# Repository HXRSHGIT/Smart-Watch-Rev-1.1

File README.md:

# Smart Watch Rev 1.1 — HealthOS Band R&D

R&D repository for the client's **HealthOS Band** (WHOOP-style wellness band with a hidden 64×32 OLED).
Source brief: [`docs/HARDWARE_ENGINEER_HANDOFF_REQUIREMENTS.md`](docs/HARDWARE_ENGINEER_HANDOFF_REQUIREMENTS.md) (copied unchanged).

Done by Harsh Thakur.

## Current design - Iteration 1

The Iteration 1 board is a **battery-less, bench-powered engineering PCB** (5 V on two pogo pads or a 2.54 mm header, no cell fitted) built around **nRF54L15 + nPM1300 + MAX86141 (SFH 7016 emitters, 2 x VEMD8080 photodiodes) + BMI270 + MAX30208 + MX25R3235F flash + a Johanson chip antenna**. Firmware is flashed and debugged over SWD (Tag-Connect). The 10-page KiCad 9 schematic, its checks and the board file are in **[`hardware/schematic/`](hardware/schematic/README.md)**; the board is designed to JLCPCB's stated limits (4 layers, 0.8 mm, ENIG), see **[`hardware/JLCPCB_DESIGN_RULES.md`](hardware/JLCPCB_DESIGN_RULES.md)**. Layout (placement and routing) has not been done yet, and the design is not a fabrication-ready or sourcing-verified BOM.

This replaces the earlier 2026-10-18 baseline (ESP32-C3-MINI-1 + MAX30102 + MAX30208, USB-powered). That baseline is kept only as history in [Iteration 1 decision](docs/ITERATION_1_DECISION.md), [Iteration 1 schematic connection plan](docs/ITERATION_1_SCHEMATIC_FLOW.md) and [Component Selection](docs/COMPONENT_SELECTION.md); those three documents describe parts that are no longer on the board.

The documents under `research/` describe the earlier full-wearable investigations. Their parts and performance estimates are **not the current Iteration 1 BOM**. The original client brief remains intact as the longer-term product reference.

## How this repo is organised

`main` holds the brief, this index, the R&D map **and all research merged in** (folders below). Each topic also stays on its **own `rnd/*` branch** for a separate view.

| Branch | Folder | Covers (brief §) |
|---|---|---|
| `rnd/components` | [`research/components/`](research/components/) | §8 — every candidate part plus alternatives, full detail (`COMPONENTS.md`) |
| `rnd/mcu-ble` | [`research/mcu-ble/`](research/mcu-ble/) | §4.6, §8 — nRF5340 vs nRF54, BLE security, DFU, antenna |
| `rnd/storage-nfc-dft` | [`research/storage-nfc-dft/`](research/storage-nfc-dft/) | §4.6, §8 — external flash, active NFC, SWD, production test |
| `rnd/power-battery` | [`research/power-battery/`](research/power-battery/) | §4.7, §8 — power tree, battery sizing, battery-life model, pogo charging, peaks |
| `rnd/display-haptics` | [`research/display-haptics/`](research/display-haptics/) | §4.4, §4.5 — OLED module, dead-front, back-power, LRA and driver |
| `rnd/optical-ppg` | [`research/optical-ppg/`](research/optical-ppg/) | §4.1, §8 — PPG HR, SpO2, optical stack, crosstalk |
| `rnd/sensors` | [`research/sensors/`](research/sensors/) | §4.1 — IMU, pressure and vent, skin temperature, time sync |
| `rnd/algorithms` | [`research/algorithms/`](research/algorithms/) | §4.2, §4.3, §5 — activity, calories, sleep, HRV and other P1 algorithms |
| `rnd/validation` | [`research/validation/`](research/validation/) | §13–15 — test plan, compliance, mechanical, RF, water and sweat |

## Earlier wearable R&D findings (historical, not the Iteration 1 baseline)

These findings are retained as research history, including assumptions and claims requiring further verification. In particular, the original PPG pulse limits, PVLED headroom reasoning, BMI270 current, NFC power assumptions and battery estimates must be rechecked before reuse. See the current decision above for what will actually be fitted now.

1. **Battery life is a PPG-settings decision.** Same hardware: ≈ 5 / 10 / 29 mAh per day for lean / typical / continuous-100-sps profiles → 5 days needs ≈ 32 / 61 / 184 mAh. Suggested target: 5 days on ≈ 150 mAh with adaptive PPG (`rnd/power-battery`).
2. **SoC: nRF54L15** (CSP if HDI is available) instead of nRF5340 — saves ≈ 50 mm²; battery difference ≈ 2 µA (`rnd/mcu-ble`).
3. **One 1.8 V digital rail.** MAX86141 is 1.8 V SPI, so swap the 3 V-only W25Q32RV flash for Macronix MX25R3235F (`rnd/storage-nfc-dft`).
4. **PPG LED supply needs ≥ 3.1 V** and cannot come from the nPM1300 bucks — VBAT direct (HR pauses near empty) or a small boost (`rnd/power-battery`, `rnd/optical-ppg`).
5. **Drop the active NFC reader** (no use case, ≈ 400 mA peak); the SoC's passive NFC tag gives tap-to-pair for free (`rnd/storage-nfc-dft`).
6. **BMI270 always-on accel (≈ 210 µA, verify) is a top load**, and it cannot do wrist-raise and tap at the same time — consider a low-power wake accelerometer (`rnd/sensors`, `rnd/display-haptics`).
7. **Stealth dead-front is not readable in direct sun**; an AR coating is the biggest improvement (`rnd/display-haptics`).
8. **SpO2 skin-tone bias is documented** — validate per Monk skin-tone group + ITA following FDA's 2025 draft study design (`rnd/optical-ppg`).
9. **Calories are the weakest output industry-wide** (27–93 % median error in published tests) — label as estimates (`rnd/algorithms`).
10. **§13 gates → 25 concrete tests**; wellness position depends on claims; water target at least IPX7 (`rnd/validation`).

## Longer-term wearable R&D map

Legend: **R&D** = open question, needs study or experiment · **Design** = known engineering, needs careful execution · **Owner** = client decision, not engineering.

| § | Point | Class | Why |
|---|---|---|---|
| 2 | Stealth dead-front vs visible OLED, same PCB | **R&D** | Transmission vs off-state blackness trade; needs material samples and measurement |
| 3 | Present all health outputs as estimates | Owner | Wording and claims policy; the sentence is cut off in the brief |
| 4.1 | Continuous / resting HR | **R&D** | Wrist PPG motion artifact; LED current vs battery |
| 4.1 | Workout HR and zones | **R&D** | HR accuracy during motion is the hardest PPG problem |
| 4.1 | Spot + sleep SpO2 | **R&D** | Reflective wrist SpO2 needs red/IR calibration against a reference; skin-tone bias |
| 4.1 | Skin temperature trend | **R&D** | Thermal isolation from PCB and battery heat; trend vs absolute |
| 4.1 | Motion data | Design | BMI270 is mature; orientation and FIFO setup |
| 4.1 | Pressure for floors | **R&D** | Waterproof breathable vent; sensitivity to wrist movement and temperature |
| 4.1 | Raw data access | Design | Logging and streaming bandwidth over BLE and flash |
| 4.1 | Sensor time sync | **R&D** | Common timebase across AFE, IMU and MCU FIFOs |
| 4.2 | Steps / distance / active min | Design | Known algorithms; tuning for wrist placement |
| 4.2 | Calories | **R&D** | Model choice (HR + motion + profile); estimate only |
| 4.2 | Floors / elevation | **R&D** | Barometer + IMU fusion |
| 4.2 | Activity classification + confidence | **R&D** | Needs a labelled dataset and an on-device model budget |
| 4.3 | Sleep detection / duration | **R&D** | Actigraphy + HR; validation vs reference |
| 4.3 | HW readiness for HRV / RR / stages | **R&D** | Sets PPG sample rate and timing jitter requirements now |
| 4.4 | 64×32 OLED module choice | **R&D** | Exact orderable module, flex, cover stack, outdoor readability |
| 4.4 | No back-power when display off | Design | Load switch + I/O state; measure leakage |
| 4.4 | Wake by gesture / tap | **R&D** | False-wake rate vs IMU power |
| 4.5 | LRA selection + patterns | **R&D** | Size, resonance, peak current, mounting in a thin band |
| 4.6 | BLE Android/iOS | Owner | Platforms to support |
| 4.6 | Secure pairing + authenticated DFU | Design | MCUboot / nRF Connect SDK; key management |
| 4.6 | External flash logging | Design | Capacity sizing vs offline days |
| 4.6 | SWD + production test access | Design | Pad plan, fixture |
| 4.7 | Battery capacity vs 5–7 days | **R&D** | Needs a duty-cycle power model, then a cell that fits the enclosure |
| 4.7 | Reversible pogo, faults | **R&D** | Bridge vs ideal-diode orientation fix, contact heating, ESD |
| 4.7 | Concurrent peak load | **R&D** | PPG pulses + radio + flash + haptic + NFC on a small cell |
| 4.7 | Charging limits | Design | Follow the cell datasheet; NTC wiring to nPM1300 |
| 5 | P1: HRV, RR, recovery, GPS, falls | **R&D** | Algorithm work; HW must not block it |
| 8 | MCU choice (nRF5340 vs nRF54) | **R&D** | Trade study before schematic freeze |
| 8 | Active NFC (ST25R210) | **R&D** | Use case unknown; power and antenna cost |
| 8 | Separate optical / NFC / display rails | **R&D** | Depends on the power model |
| 13 | Acceptance gates | Design | Test plan and fixtures per gate |

## Gaps in the brief

- Sections **6, 7, 9, 10, 11 and 12 are missing** (numbering jumps 5 → 8 → 13). Probably owner decisions, targets and deliverables. Ask the client.
- §3 is cut off mid-sentence: "…must be presented as estimates until the complete product".
- Open owner decisions: phone platforms, battery-life target, NFC use case, display module, water-resistance target.

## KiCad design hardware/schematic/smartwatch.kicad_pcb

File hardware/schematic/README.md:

# HealthOS Band main board: KiCad schematic

Done by Harsh Thakur.

KiCad 9 project, hierarchical. Open `smartwatch.kicad_pro`.

The sheets are drawn the way a person draws them: real wires between parts, left-to-right signal flow, frames with headings, blue designer notes, one ground symbol per group. Net labels are used only where a wire cannot reach: the I2C pair at the second chip on the sensors sheet, and on the root page the second receiver of the SPI bus (memory) and of the I2C bus (power), 10 labels. Bus test points sit on the sheets that own the bus. The rules are in `STYLE_GUIDE.md`; the datasheet review is in `REVIEW.md`. Each sheet is a script in `tools/sheets/`. Supply rails are power symbols, so they connect by name across sheets.

## Sheets

| Sheet | File | Contents | State |
|---|---|---|---|
| Root | `smartwatch.kicad_sch` | sheet blocks and the signals between them | done |
| Charging input | `input_protection.kicad_sch` | two pogo pads, OCVPB21-13F6, RLIM, COUT, FLAG pull-up | done |
| LED supply | `led_supply.kicad_sch` | TPS61240 5 V boost, 0 Ohm links to VLED (boost or VSYS) | done |
| MCU | `mcu.kicad_sch` | nRF54L15 (3 units), decoupling, DC/DC, crystals, reset, debug | done |
| RF | `rf.kicad_sch` | Nordic match network, antenna tee, Johanson antenna | done |
| Optical | `optical.kicad_sch` | MAX86141, SFH 7016, 2 x VEMD8080 | done |
| Sensors | `sensors.kicad_sch` | BMI270, MAX30208, I2C pull-ups | done |
| Test | `test.kicad_sch` | Tag-Connect SWD pads, test points | done |
| Power | `power.kicad_sch` | nPM1300 (QFN32), L6, caps, battery connector, NTC, ship-mode button | done |
| Memory | `memory.kicad_sch` | MX25R3235F (8-land USON), CS# pull-up, SPI test points | done |

## Rebuild and check

```
python tools/gen_footprints.py     # custom footprints -> libs/smartwatch.pretty
python tools/build.py              # symbols and sheets
python tools/check.py              # ERC + netlist vs expected + pin table + footprint pads
python tools/lint.py               # wire crossings and net labels per sheet
python tools/pinmap.py             # PIN_MAP.md and BOM.csv
python tools/dev.py mcu A3 110     # preview one sheet as build/dev/mcu.png
```

`check.py` needs `kicad-cli` (KiCad 9). It prints `ALL CHECKS PASSED` or the list of differences.

## What the check covers

1. KiCad ERC on the whole hierarchy: zero messages.
2. Every pin of the nRF54L15, nPM1300, MX25R3235F, MAX86141, SFH 7016, VEMD8080, BMI270, MAX30208, TPS61240, OCVPB21, antenna, battery connector, button and programming pads is on the net the requirements document says. The expected table is typed separately from the build script.
3. Every two-pin part by reference (both nets; the pin order of a passive does not matter, so the check follows each chain of parts from the nets it already knows), 61 of them. Internal nets are compared by connectivity, not by name, because wired nets carry no label.
4. The nRF54L15 symbol has the same 49 pin numbers and names as the datasheet pin table (`data/nrf54l15_qfn48_pins.csv`).
5. Every footprint pad matches the symbol pins (stock and custom footprints).
6. No net has a single pin.

## nRF54L15 pin plan

| Pins | Use |
|---|---|
| P2.01 SCK, P2.02 MOSI, P2.04 MISO | SPI bus (SPIM00, dedicated pins) to MAX86141 and the flash |
| P2.05 | chip select, MAX86141 |
| P2.00 | chip select, flash |
| P0.04 SCL, P0.03 SDA | I2C (TWIM30) to BMI270, MAX30208 and the nPM1300 (0x6B) |
| P0.01, P0.02 | BMI270 INT1, BMI270 INT2 (P0.00 is free: the MAX86141 INT is not wired, see `../JLCPCB_DESIGN_RULES.md`) |
| P2.03 | MAX30208 alarm (GPIO0) |
| P1.08 | nPM1300 interrupt (GPIO1) |
| P2.06 | OCVPB21 FLAG |
| P2.08 | LED boost enable |
| P2.09, P2.10 | free (the MAX86141 GPIO1 and GPIO2 are not wired) |
| P2.07 | SWO (trace output to the test pads) |
| P1.00, P1.01 | 32.768 kHz crystal |
| P1.02, P1.03 | NFC pins, unused |
| P1.04 to P1.07, P1.09 to P1.14 | unused (errata 100 on power-on shorts) |

## Known open items (also in `../REQUIREMENTS_FROM_DATASHEETS.md` section 12)

- nPM1300 and flash datasheets are not saved yet, so those two sheets and the power budget are not built.
- Footprint status is in `../FOOTPRINT_AUDIT.md`. Still open: the OCVPB21 dot-to-A1 link (confirm on the first parts), the VEMD8080 anode pad (closed by decision, prove with a diode test on a sample part), the pogo pad size (dock vendor), J4 (not fitted).
- Tag-Connect TC2030 pin order (1 VTREF, 2 SWDIO, 3 nRESET, 4 SWDCLK, 5 GND, 6 SWO) is confirmed against the TC2030-CTX cable drawing.
- Passive part numbers are not chosen yet; values and ratings come from the datasheets.

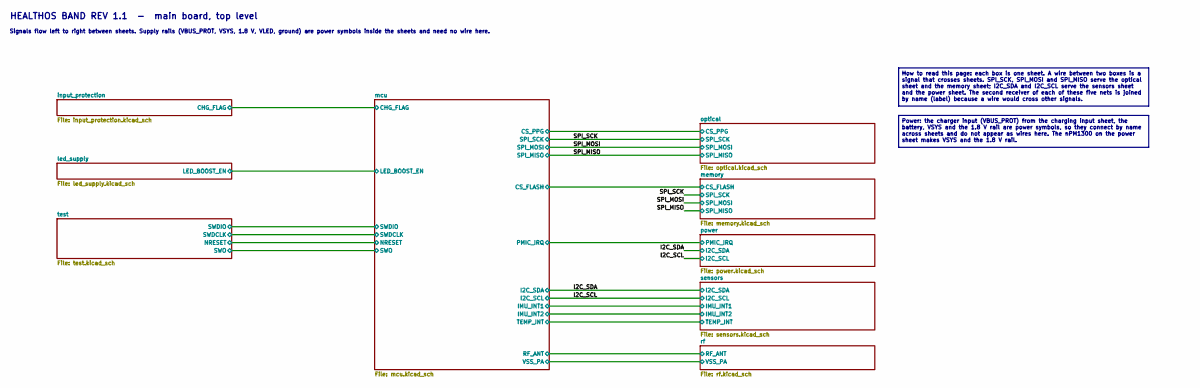
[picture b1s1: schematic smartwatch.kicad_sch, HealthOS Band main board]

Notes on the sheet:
HEALTHOS BAND REV 1.1 - main board, top level
Signals flow left to right between sheets. Supply rails (VBUS_PROT, VSYS, 1.8 V, VLED, ground) are power symbols inside the sheets and need no wire here.
How to read this page: each box is one sheet. A wire between two boxes is a signal that crosses sheets. SPI_SCK, SPI_MOSI and SPI_MISO serve the optical sheet and the memory sheet; I2C_SDA and I2C_SCL serve the sensors sheet and the power sheet. The second receiver of each of these five nets is joi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
Power: the charger input (VBUS_PROT) from the charging input sheet, the battery, VSYS and the 1.8 V rail are power symbols, so they connect by name across sheets and do not appear as wires here. The nPM1300 on the power sheet makes VSYS and the 1.8 V rail.

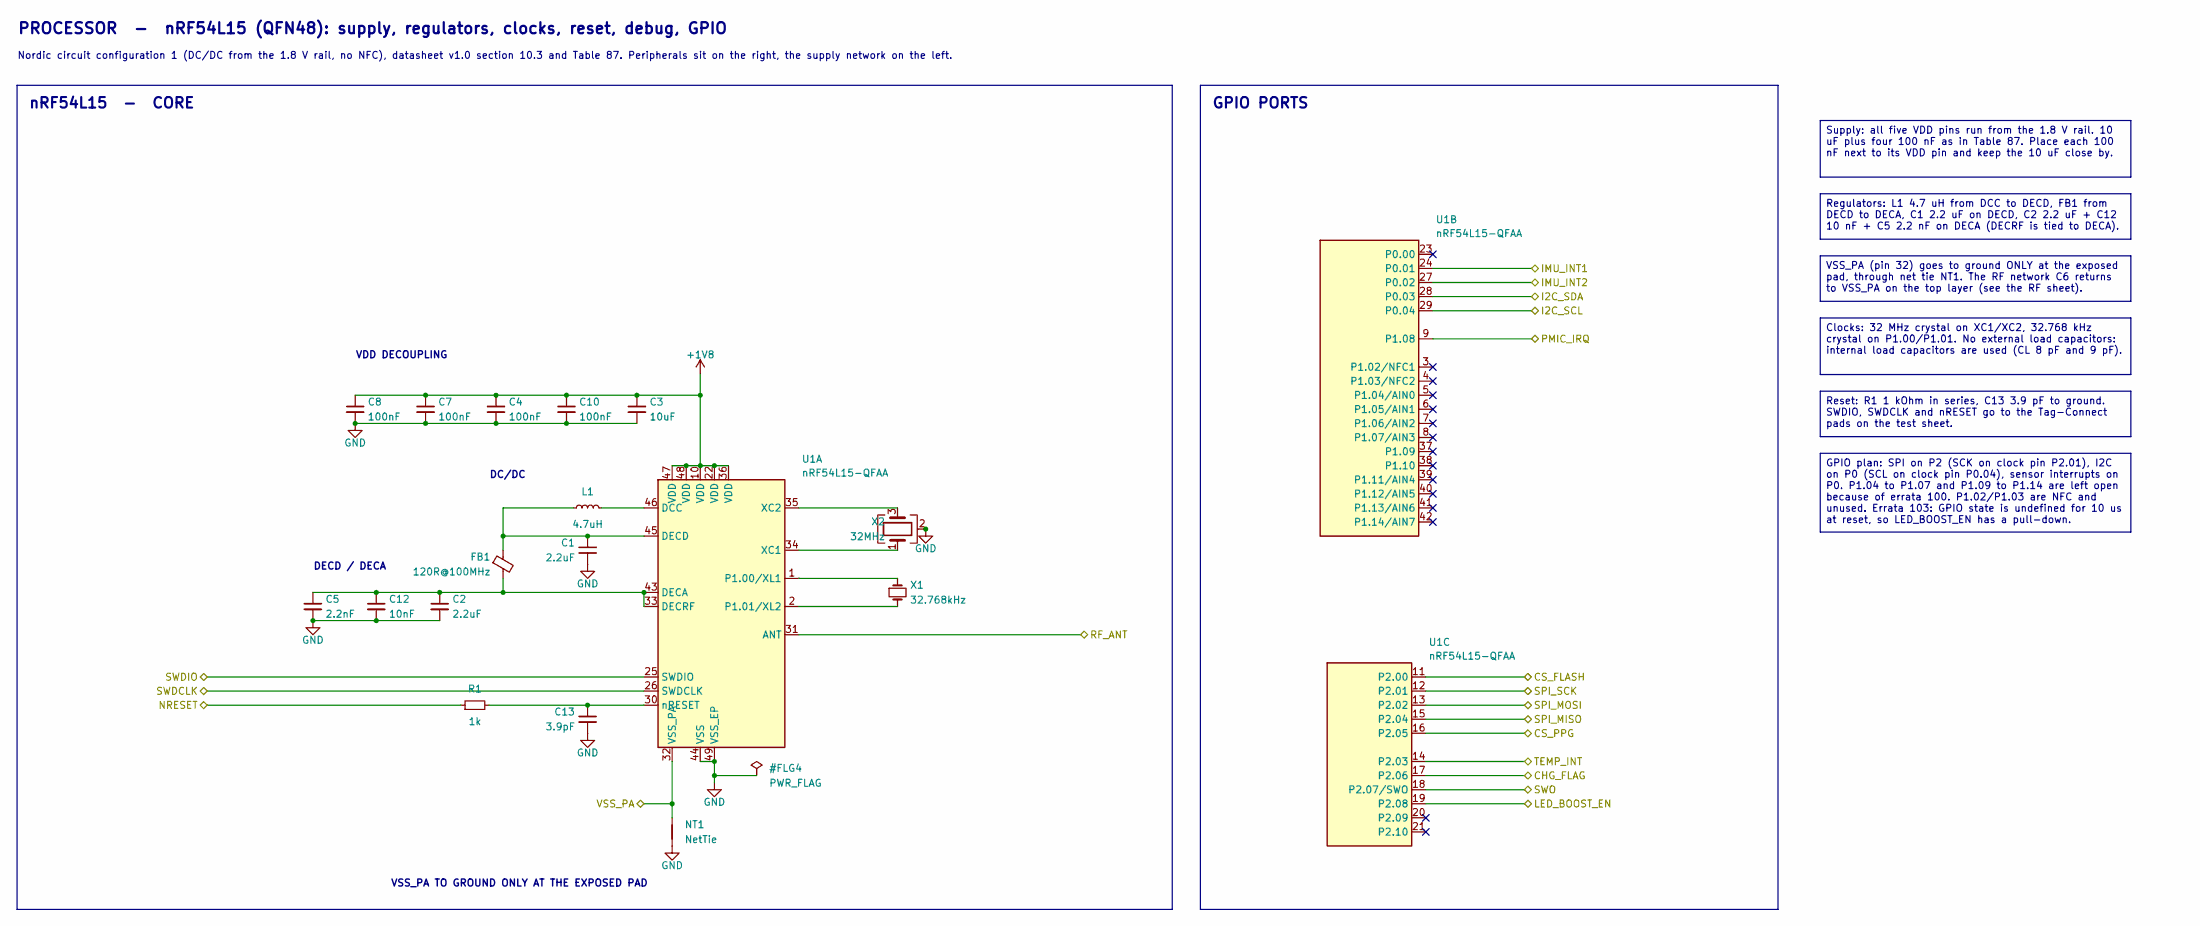
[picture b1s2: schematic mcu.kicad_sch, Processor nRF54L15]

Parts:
C1, C2: 2.2uF; C_0201_0603Metric
C3: 10uF; C_0402_1005Metric
C4, C7, C8, C10: 100nF; C_0201_0603Metric
C5: 2.2nF; C_0201_0603Metric
C12: 10nF; C_0201_0603Metric
C13: 3.9pF; C_0201_0603Metric
FB1: 120R@100MHz; L_0201_0603Metric
L1: 4.7uH; L_0603_1608Metric
NT1: NetTie; NetTie-2_SMD_Pad0.5mm
R1: 1k; R_0201_0603Metric
U1: nRF54L15-QFAA; QFN-48-1EP_6x6mm_P0.4mm_EP4.6x4.6mm
X1: 32.768kHz; Crystal_SMD_2012_SC-20S_2.05x1.2mm; MPN SC-20S 32.768kHz 9pF 20ppm
X2: 32MHz; Crystal_SMD_2016-4Pin_2.0x1.6mm; MPN NX2016SA-32MHZ-EXS00A-CS06654

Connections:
+1V8: C3.1, C4.1, C7.1, C8.1, C10.1, U1.10 (VDD), U1.22 (VDD), U1.36 (VDD), U1.47 (VDD), U1.48 (VDD); also elsewhere on the board
/I2C_SCL: U1.29 (P0.04); also elsewhere on the board
/I2C_SDA: U1.28 (P0.03); also elsewhere on the board
/SPI_MISO: U1.15 (P2.04); also elsewhere on the board
/SPI_MOSI: U1.13 (P2.02); also elsewhere on the board
/SPI_SCK: U1.12 (P2.01); also elsewhere on the board
/input_protection/CHG_FLAG: U1.17 (P2.06); also elsewhere on the board
/led_supply/LED_BOOST_EN: U1.19 (P2.08); also elsewhere on the board
/mcu/CS_FLASH: U1.11 (P2.00); also elsewhere on the board
/mcu/CS_PPG: U1.16 (P2.05); also elsewhere on the board
/mcu/IMU_INT1: U1.24 (P0.01); also elsewhere on the board
/mcu/IMU_INT2: U1.27 (P0.02); also elsewhere on the board
/mcu/NRESET: R1.1; also elsewhere on the board
/mcu/PMIC_IRQ: U1.9 (P1.08); also elsewhere on the board
/mcu/RF_ANT: U1.31 (ANT); also elsewhere on the board
/mcu/SWDCLK: U1.26 (SWDCLK); also elsewhere on the board
/mcu/SWDIO: U1.25 (SWDIO); also elsewhere on the board
/mcu/SWO: U1.18 (P2.07/SWO); also elsewhere on the board
/mcu/TEMP_INT: U1.14 (P2.03); also elsewhere on the board
/mcu/VSS_PA: NT1.2, U1.32 (VSS_PA); also elsewhere on the board
GND: C1.2, C2.2, C3.2, C4.2, C5.2, C7.2, C8.2, C10.2, C12.2, C13.2, NT1.1, U1.44 (VSS), U1.49 (VSS_EP), X2.2 (G), X2.4 (G); also elsewhere on the board
unnamed: L1.2, U1.46 (DCC)
unnamed: C2.1, C5.1, C12.1, FB1.2, U1.33 (DECRF), U1.43 (DECA)
unnamed: C1.1, FB1.1, L1.1, U1.45 (DECD)
unnamed: U1.1 (P1.00/XL1), X1.1
unnamed: U1.2 (P1.01/XL2), X1.2
unnamed: U1.34 (XC1), X2.1
unnamed: U1.35 (XC2), X2.3
unnamed: C13.1, R1.2, U1.30 (nRESET)

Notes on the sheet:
PROCESSOR - nRF54L15 (QFN48): supply, regulators, clocks, reset, debug, GPIO
Nordic circuit configuration 1 (DC/DC from the 1.8 V rail, no NFC), datasheet v1.0 section 10.3 and Table 87. Peripherals sit on the right, the supply network on the left.
nRF54L15 - CORE
GPIO PORTS
VDD DECOUPLING
DECD / DECA
DC/DC
VSS_PA TO GROUND ONLY AT THE EXPOSED PAD
Supply: all five VDD pins run from the 1.8 V rail. 10 uF plus four 100 nF as in Table 87. Place each 100 nF next to its VDD pin and keep the 10 uF close by.
Regulators: L1 4.7 uH from DCC to DECD, FB1 from DECD to DECA, C1 2.2 uF on DECD, C2 2.2 uF + C12 10 nF + C5 2.2 nF on DECA (DECRF is tied to DECA).
VSS_PA (pin 32) goes to ground ONLY at the exposed pad, through net tie NT1. The RF network C6 returns to VSS_PA on the top layer (see the RF sheet).
Clocks: 32 MHz crystal on XC1/XC2, 32.768 kHz crystal on P1.00/P1.01. No external load capacitors: internal load capacitors are used (CL 8 pF and 9 pF).
Reset: R1 1 kOhm in series, C13 3.9 pF to ground. SWDIO, SWDCLK and nRESET go to the Tag-Connect pads on the test sheet.
GPIO plan: SPI on P2 (SCK on clock pin P2.01), I2C on P0 (SCL on clock pin P0.04), sensor interrupts on P0. P1.04 to P1.07 and P1.09 to P1.14 are left open because of errata 100. P1.02/P1.03 are NFC and unused. Errata 103: GPIO state is undefined for 10 us at reset, so LED_BOOST_EN has a pull-down.

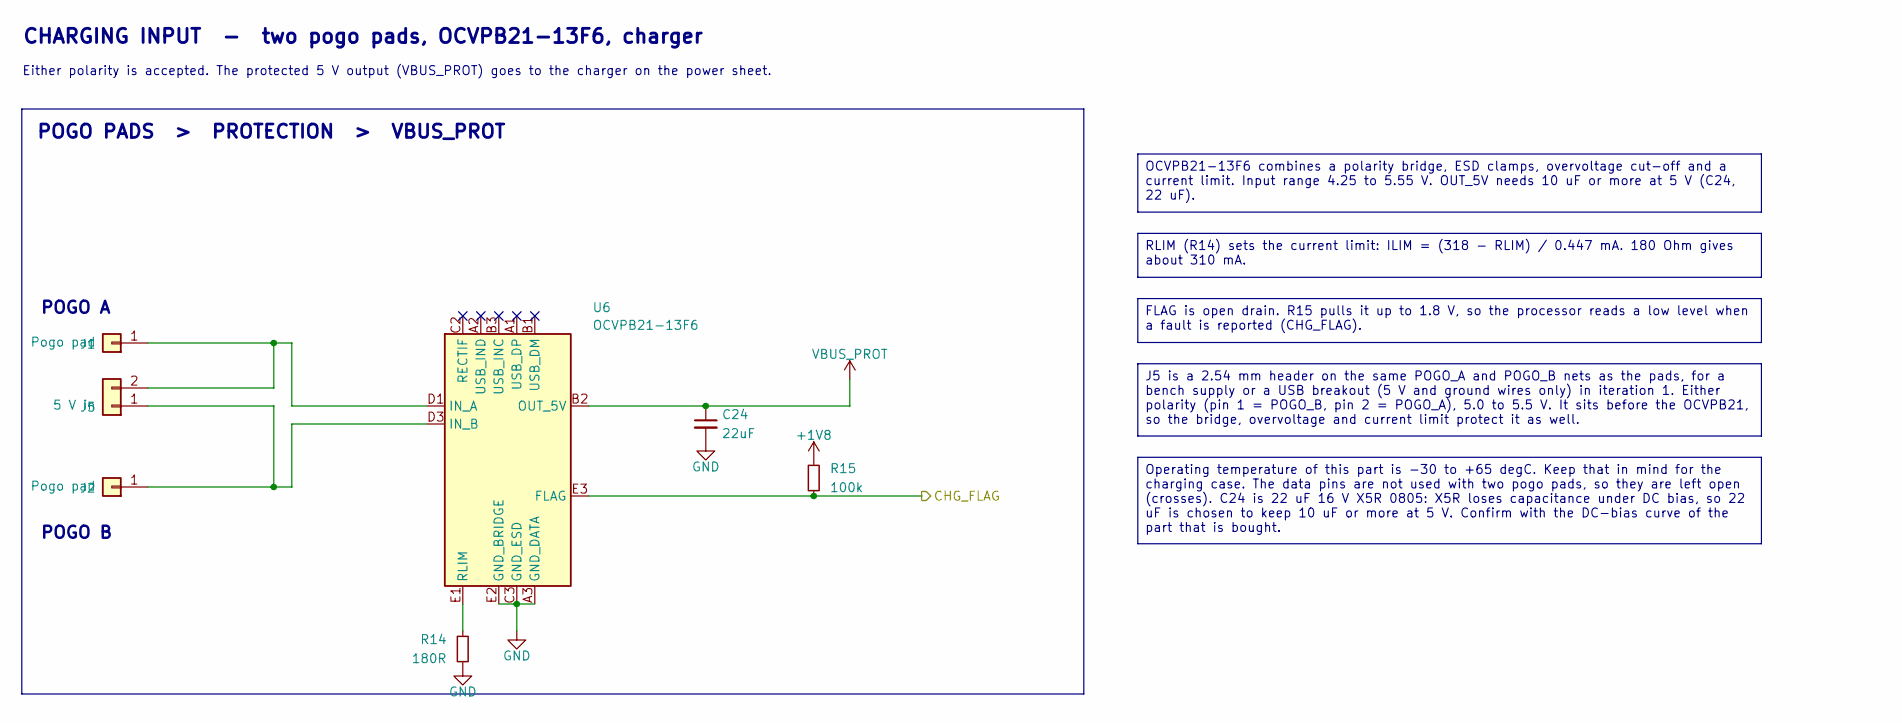
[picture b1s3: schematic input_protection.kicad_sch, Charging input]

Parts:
C24: 22uF; C_0805_2012Metric
J1, J2: Pogo pad; Pogo_Pad_D2.6mm
J5: 5 V in; PinHeader_1x02_P2.54mm_Vertical
R14: 180R; R_0402_1005Metric
R15: 100k; R_0201_0603Metric
U6: OCVPB21-13F6; OCVPB21-13F6_WLCSP-13_P0.4mm

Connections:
+1V8: R15.1; also elsewhere on the board
/input_protection/CHG_FLAG: R15.2, U6.E3 (FLAG); also elsewhere on the board
GND: C24.2, R14.2, U6.A3 (GND_DATA), U6.C3 (GND_ESD), U6.E2 (GND_BRIDGE); also elsewhere on the board
unnamed: J1.1, J5.2, U6.D1 (IN_A)
unnamed: J2.1, J5.1, U6.D3 (IN_B)
unnamed: R14.1, U6.E1 (RLIM)
VBUS_PROT: C24.1, U6.B2 (OUT_5V); also elsewhere on the board

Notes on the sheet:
CHARGING INPUT - two pogo pads, OCVPB21-13F6, charger
Either polarity is accepted. The protected 5 V output (VBUS_PROT) goes to the charger on the power sheet.
POGO PADS > PROTECTION > VBUS_PROT
POGO A
POGO B
OCVPB21-13F6 combines a polarity bridge, ESD clamps, overvoltage cut-off and a current limit. Input range 4.25 to 5.55 V. OUT_5V needs 10 uF or more at 5 V (C24, 22 uF).
RLIM (R14) sets the current limit: ILIM = (318 - RLIM) / 0.447 mA. 180 Ohm gives about 310 mA.
FLAG is open drain. R15 pulls it up to 1.8 V, so the processor reads a low level when a fault is reported (CHG_FLAG).
J5 is a 2.54 mm header on the same POGO_A and POGO_B nets as the pads, for a bench supply or a USB breakout (5 V and ground wires only) in iteration 1. Either polarity (pin 1 = POGO_B, pin 2 = POGO_A), 5.0 to 5.5 V. It sits before the OCVPB21, so the bridge, overvoltage and current limit protect it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
Operating temperature of this part is -30 to +65 degC. Keep that in mind for the charging case. The data pins are not used with two pogo pads, so they are left open (crosses). C24 is 22 uF 16 V X5R 0805: X5R loses capacitance under DC bias, so 22 uF is chosen to keep 10 uF or more at 5 V. Confirm w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

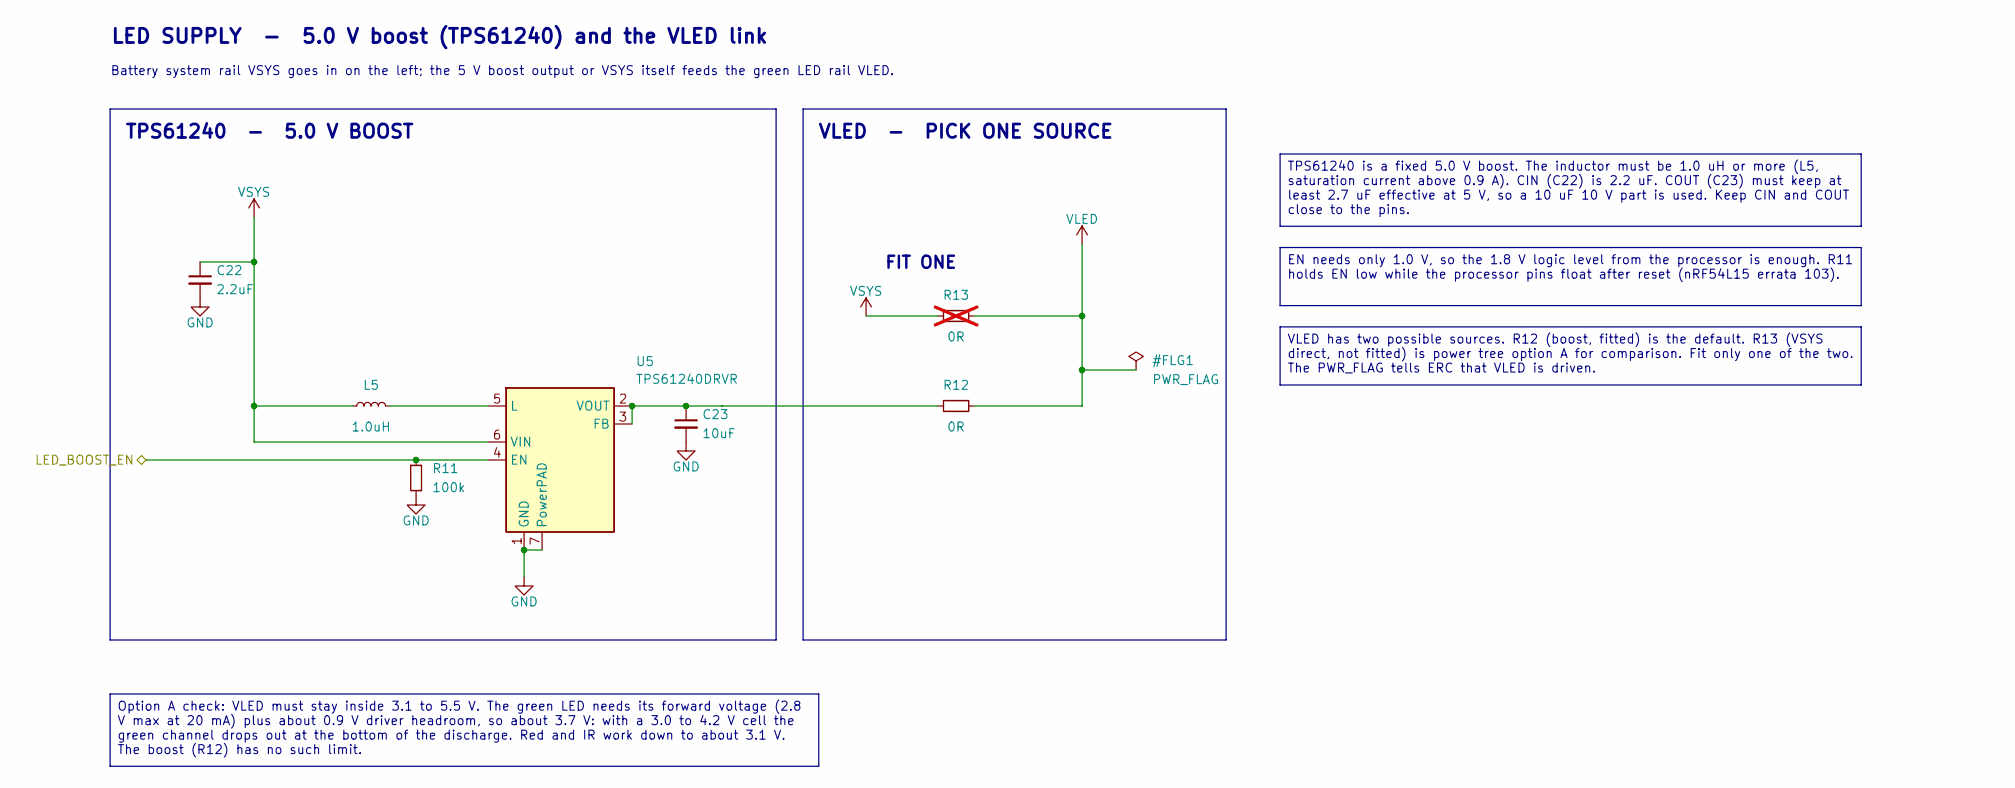
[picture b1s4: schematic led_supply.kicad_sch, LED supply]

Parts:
C22: 2.2uF; C_0402_1005Metric
C23: 10uF; C_0603_1608Metric
L5: 1.0uH; L_0805_2012Metric; MPN LQM21PN1R0MC0
R11: 100k; R_0201_0603Metric
R12: 0R; R_0402_1005Metric
R13: 0R; R_0402_1005Metric; not fitted
U5: TPS61240DRVR; WSON-6-1EP_2x2mm_P0.65mm_EP1x1.6mm

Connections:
/led_supply/LED_BOOST_EN: R11.1, U5.4 (EN); also elsewhere on the board
GND: C22.2, C23.2, R11.2, U5.1 (GND), U5.7 (PowerPAD); also elsewhere on the board
unnamed: C23.1, R12.1, U5.2 (VOUT), U5.3 (FB)
unnamed: L5.2, U5.5 (L)
VLED: R12.2, R13.2; also elsewhere on the board
VSYS: C22.1, L5.1, R13.1, U5.6 (VIN); also elsewhere on the board

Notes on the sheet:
LED SUPPLY - 5.0 V boost (TPS61240) and the VLED link
Battery system rail VSYS goes in on the left; the 5 V boost output or VSYS itself feeds the green LED rail VLED.
TPS61240 - 5.0 V BOOST
VLED - PICK ONE SOURCE
FIT ONE
TPS61240 is a fixed 5.0 V boost. The inductor must be 1.0 uH or more (L5, saturation current above 0.9 A). CIN (C22) is 2.2 uF. COUT (C23) must keep at least 2.7 uF effective at 5 V, so a 10 uF 10 V part is used. Keep CIN and COUT close to the pins.
EN needs only 1.0 V, so the 1.8 V logic level from the processor is enough. R11 holds EN low while the processor pins float after reset (nRF54L15 errata 103).
VLED has two possible sources. R12 (boost, fitted) is the default. R13 (VSYS direct, not fitted) is power tree option A for comparison. Fit only one of the two. The PWR_FLAG tells ERC that VLED is driven.
Option A check: VLED must stay inside 3.1 to 5.5 V. The green LED needs its forward voltage (2.8 V max at 20 mA) plus about 0.9 V driver headroom, so about 3.7 V: with a 3.0 to 4.2 V cell the green channel drops out at the bottom of the discharge. Red and IR work down to about 3.1 V. The boost (R12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

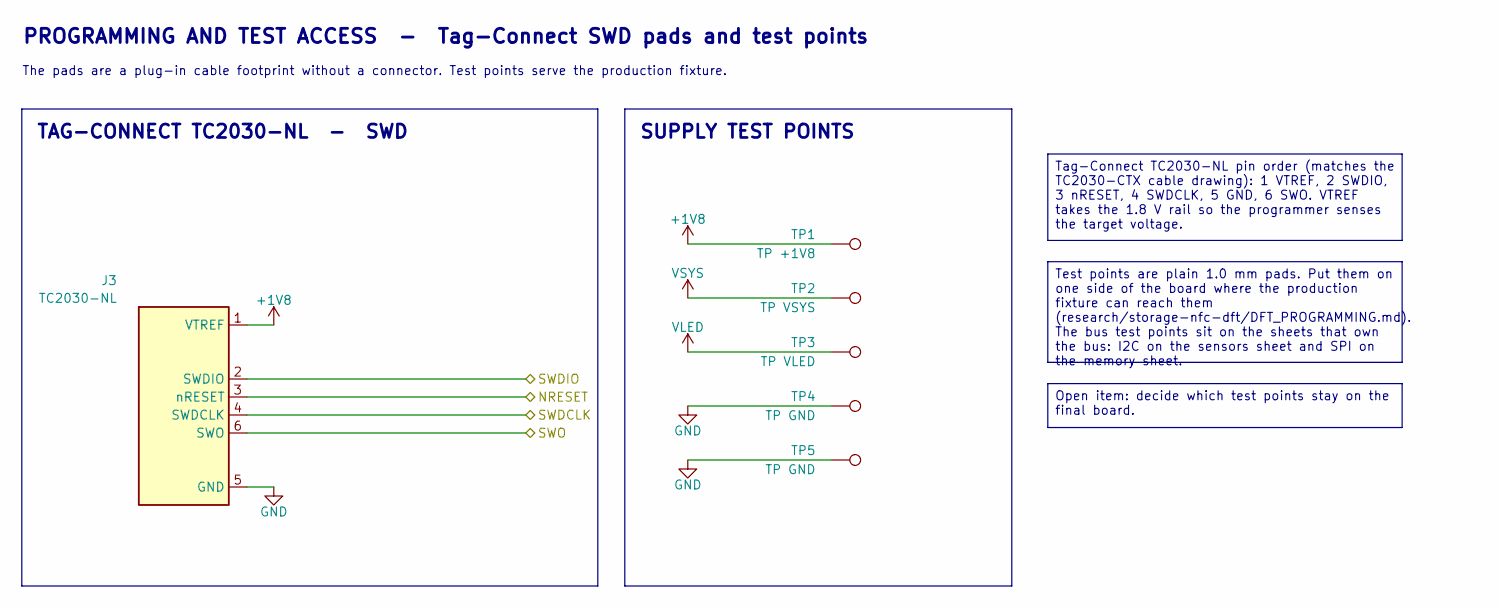
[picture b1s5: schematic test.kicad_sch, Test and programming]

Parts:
J3: TC2030-NL; Tag-Connect_TC2030-IDC-NL_2x03_P1.27mm_Vertical
TP1: TP +1V8; TestPoint_Pad_D1.0mm
TP2: TP VSYS; TestPoint_Pad_D1.0mm
TP3: TP VLED; TestPoint_Pad_D1.0mm
TP4, TP5: TP GND; TestPoint_Pad_D1.0mm

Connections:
+1V8: J3.1 (VTREF), TP1.1; also elsewhere on the board
/mcu/NRESET: J3.3 (nRESET); also elsewhere on the board
/mcu/SWDCLK: J3.4 (SWDCLK); also elsewhere on the board
/mcu/SWDIO: J3.2 (SWDIO); also elsewhere on the board
/mcu/SWO: J3.6 (SWO); also elsewhere on the board
GND: J3.5 (GND), TP4.1, TP5.1; also elsewhere on the board
VLED: TP3.1; also elsewhere on the board
VSYS: TP2.1; also elsewhere on the board

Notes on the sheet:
PROGRAMMING AND TEST ACCESS - Tag-Connect SWD pads and test points
The pads are a plug-in cable footprint without a connector. Test points serve the production fixture.
TAG-CONNECT TC2030-NL - SWD
SUPPLY TEST POINTS
Tag-Connect TC2030-NL pin order (matches the TC2030-CTX cable drawing): 1 VTREF, 2 SWDIO, 3 nRESET, 4 SWDCLK, 5 GND, 6 SWO. VTREF takes the 1.8 V rail so the programmer senses the target voltage.
Test points are plain 1.0 mm pads. Put them on one side of the board where the production fixture can reach them (research/storage-nfc-dft/DFT_PROGRAMMING.md). The bus test points sit on the sheets that own the bus: I2C on the sensors sheet and SPI on the memory sheet.
Open item: decide which test points stay on the final board.

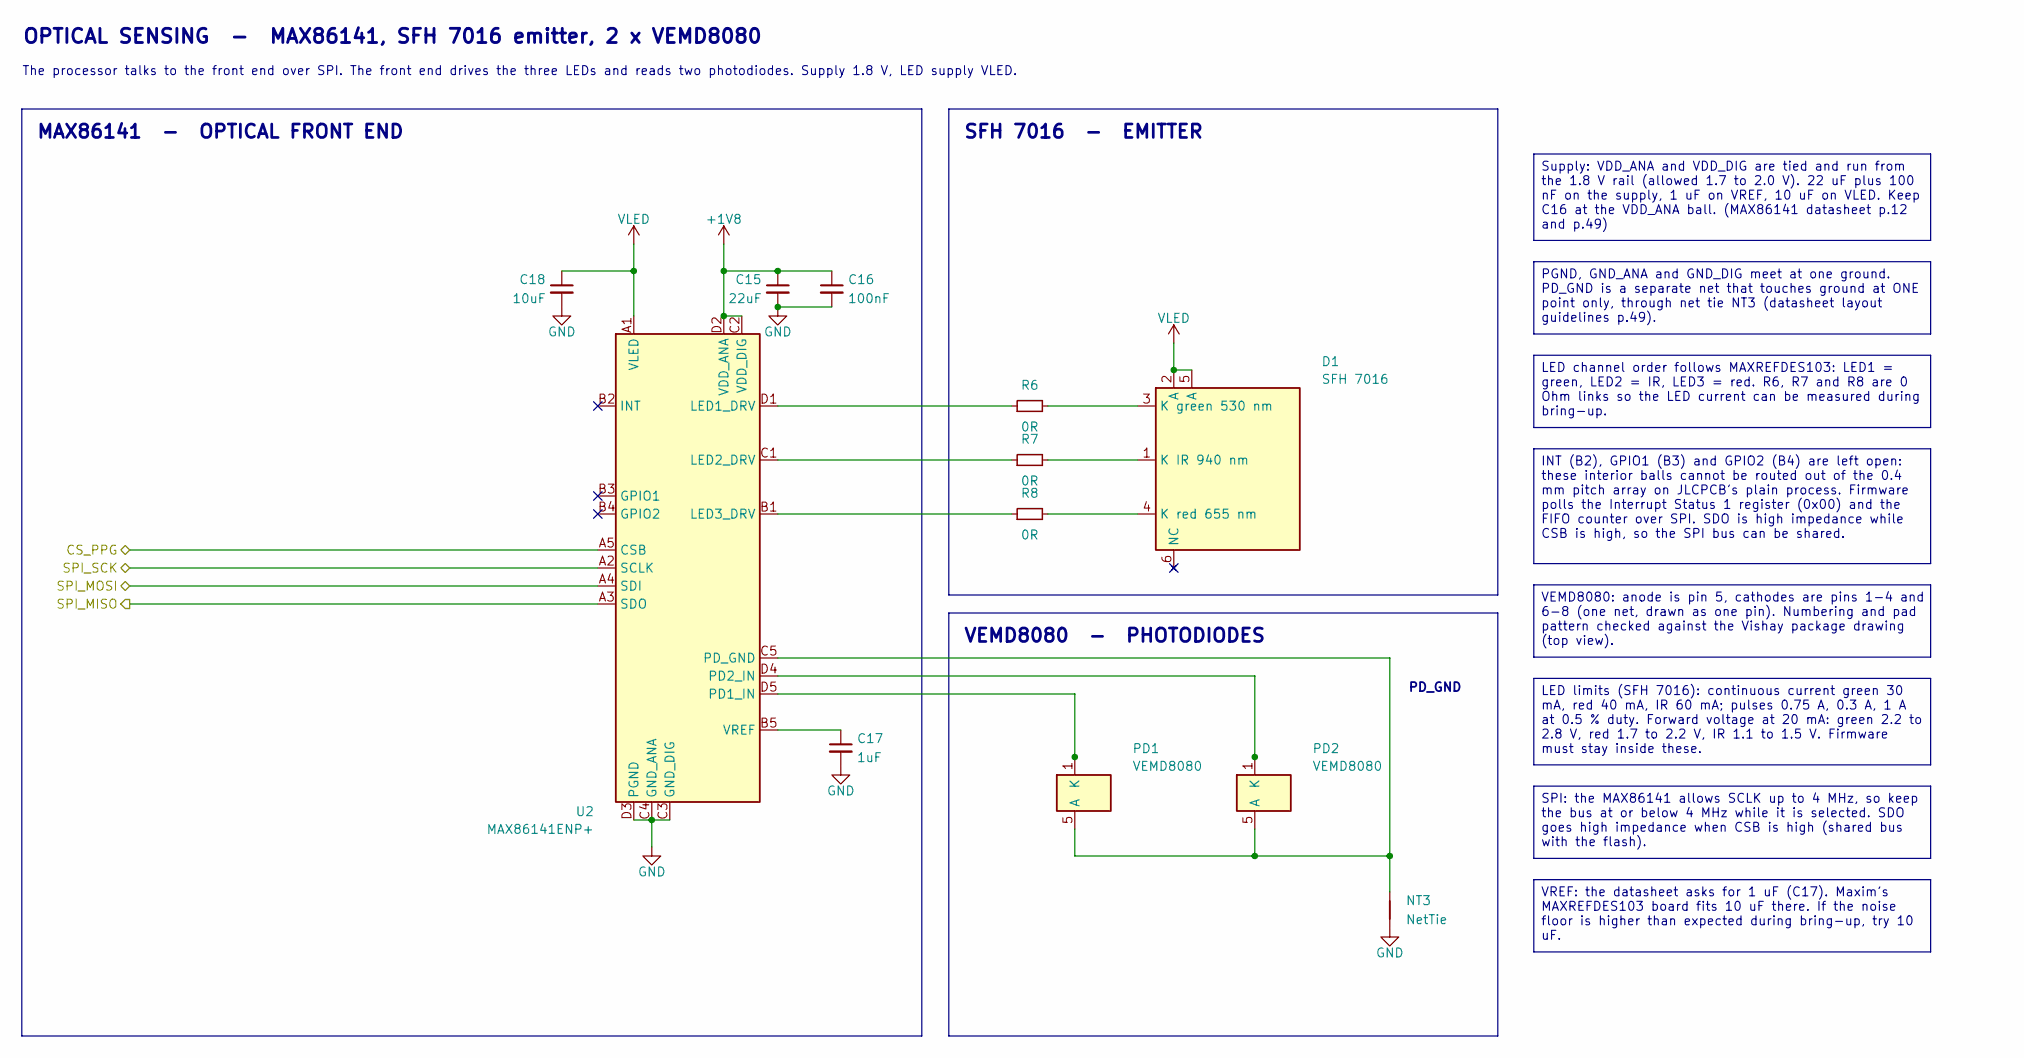
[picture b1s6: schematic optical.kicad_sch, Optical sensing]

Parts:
C15: 22uF; C_0402_1005Metric
C16: 100nF; C_0201_0603Metric
C17: 1uF; C_0201_0603Metric
C18: 10uF; C_0603_1608Metric
D1: SFH 7016; SFH7016_1.85x1.65mm
NT3: NetTie; NetTie-2_SMD_Pad0.5mm
PD1, PD2: VEMD8080; VEMD8080_4.8x2.5mm
R6, R7, R8: 0R; R_0201_0603Metric
U2: MAX86141ENP+; MAX86141_WLP-20_2.048x1.848mm_P0.4mm

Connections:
+1V8: C15.1, C16.1, U2.C2 (VDD_DIG), U2.D2 (VDD_ANA); also elsewhere on the board
/SPI_MISO: U2.A3 (SDO); also elsewhere on the board
/SPI_MOSI: U2.A4 (SDI); also elsewhere on the board
/SPI_SCK: U2.A2 (SCLK); also elsewhere on the board
/mcu/CS_PPG: U2.A5 (CSB); also elsewhere on the board
GND: C15.2, C16.2, C17.2, C18.2, NT3.1, U2.C3 (GND_DIG), U2.C4 (GND_ANA), U2.D3 (PGND); also elsewhere on the board
unnamed: D1.1 (K IR 940 nm), R7.2
unnamed: D1.3 (K green 530 nm), R6.2
unnamed: D1.4 (K red 655 nm), R8.2
unnamed: NT3.2, PD1.5 (A), PD2.5 (A), U2.C5 (PD_GND)
unnamed: R6.1, U2.D1 (LED1_DRV)
unnamed: R7.1, U2.C1 (LED2_DRV)
unnamed: R8.1, U2.B1 (LED3_DRV)
unnamed: PD1.1 (K), PD1.2 (K), PD1.3 (K), PD1.4 (K), PD1.6 (K), PD1.7 (K), PD1.8 (K), U2.D5 (PD1_IN)
unnamed: PD2.1 (K), PD2.2 (K), PD2.3 (K), PD2.4 (K), PD2.6 (K), PD2.7 (K), PD2.8 (K), U2.D4 (PD2_IN)
unnamed: C17.1, U2.B5 (VREF)
VLED: C18.1, D1.2 (A), D1.5 (A), U2.A1 (VLED); also elsewhere on the board

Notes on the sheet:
OPTICAL SENSING - MAX86141, SFH 7016 emitter, 2 x VEMD8080
The processor talks to the front end over SPI. The front end drives the three LEDs and reads two photodiodes. Supply 1.8 V, LED supply VLED.
MAX86141 - OPTICAL FRONT END
SFH 7016 - EMITTER
VEMD8080 - PHOTODIODES
PD_GND
Supply: VDD_ANA and VDD_DIG are tied and run from the 1.8 V rail (allowed 1.7 to 2.0 V). 22 uF plus 100 nF on the supply, 1 uF on VREF, 10 uF on VLED. Keep C16 at the VDD_ANA ball. (MAX86141 datasheet p.12 and p.49)
PGND, GND_ANA and GND_DIG meet at one ground. PD_GND is a separate net that touches ground at ONE point only, through net tie NT3 (datasheet layout guidelines p.49).
LED channel order follows MAXREFDES103: LED1 = green, LED2 = IR, LED3 = red. R6, R7 and R8 are 0 Ohm links so the LED current can be measured during bring-up.
INT (B2), GPIO1 (B3) and GPIO2 (B4) are left open: these interior balls cannot be routed out of the 0.4 mm pitch array on JLCPCB's plain process. Firmware polls the Interrupt Status 1 register (0x00) and the FIFO counter over SPI. SDO is high impedance while CSB is high, so the SPI bus can be share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
VEMD8080: anode is pin 5, cathodes are pins 1-4 and 6-8 (one net, drawn as one pin). Numbering and pad pattern checked against the Vishay package drawing (top view).
LED limits (SFH 7016): continuous current green 30 mA, red 40 mA, IR 60 mA; pulses 0.75 A, 0.3 A, 1 A at 0.5 % duty. Forward voltage at 20 mA: green 2.2 to 2.8 V, red 1.7 to 2.2 V, IR 1.1 to 1.5 V. Firmware must stay inside these.
SPI: the MAX86141 allows SCLK up to 4 MHz, so keep the bus at or below 4 MHz while it is selected. SDO goes high impedance when CSB is high (shared bus with the flash).
VREF: the datasheet asks for 1 uF (C17). Maxim's MAXREFDES103 board fits 10 uF there. If the noise floor is higher than expected during bring-up, try 10 uF.

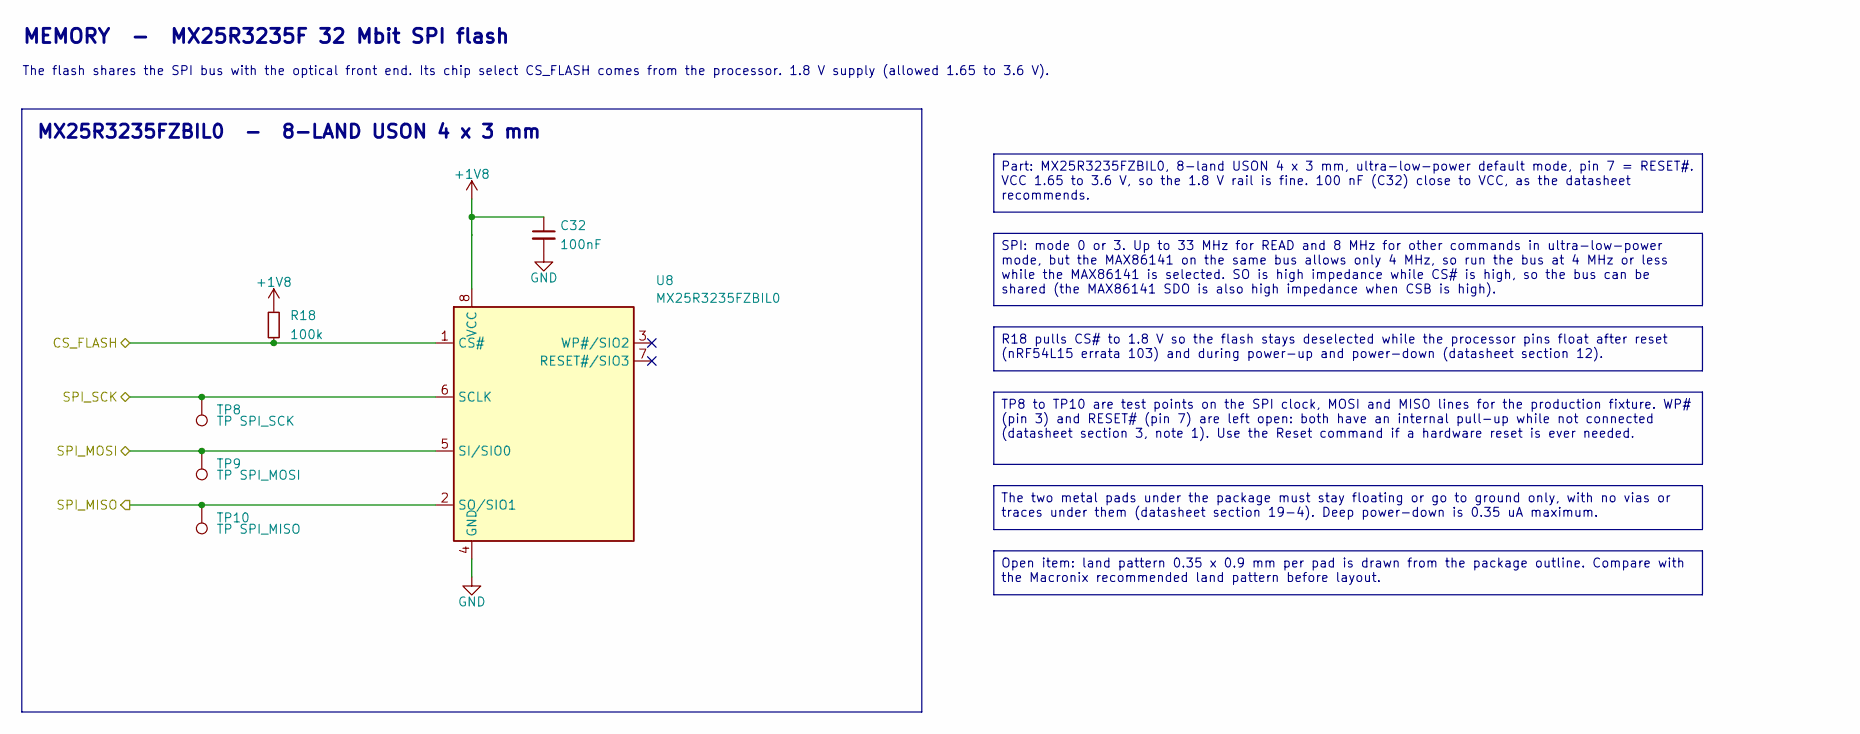
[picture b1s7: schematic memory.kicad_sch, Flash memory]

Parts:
C32: 100nF; C_0201_0603Metric
R18: 100k; R_0201_0603Metric
TP8: TP SPI_SCK; TestPoint_Pad_D1.0mm
TP9: TP SPI_MOSI; TestPoint_Pad_D1.0mm
TP10: TP SPI_MISO; TestPoint_Pad_D1.0mm
U8: MX25R3235FZBIL0; MX25R3235F_USON-8_4x3mm_P0.8mm

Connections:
+1V8: C32.1, R18.1, U8.8 (VCC); also elsewhere on the board
/SPI_MISO: TP10.1, U8.2 (SO/SIO1); also elsewhere on the board
/SPI_MOSI: TP9.1, U8.5 (SI/SIO0); also elsewhere on the board
/SPI_SCK: TP8.1, U8.6 (SCLK); also elsewhere on the board
/mcu/CS_FLASH: R18.2, U8.1 (CS#); also elsewhere on the board
GND: C32.2, U8.4 (GND); also elsewhere on the board

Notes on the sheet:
MEMORY - MX25R3235F 32 Mbit SPI flash
The flash shares the SPI bus with the optical front end. Its chip select CS_FLASH comes from the processor. 1.8 V supply (allowed 1.65 to 3.6 V).
MX25R3235FZBIL0 - 8-LAND USON 4 x 3 mm
Part: MX25R3235FZBIL0, 8-land USON 4 x 3 mm, ultra-low-power default mode, pin 7 = RESET#. VCC 1.65 to 3.6 V, so the 1.8 V rail is fine. 100 nF (C32) close to VCC, as the datasheet recommends.
SPI: mode 0 or 3. Up to 33 MHz for READ and 8 MHz for other commands in ultra-low-power mode, but the MAX86141 on the same bus allows only 4 MHz, so run the bus at 4 MHz or less while the MAX86141 is selected. SO is high impedance while CS# is high, so the bus can be shared (the MAX86141 SDO is als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
R18 pulls CS# to 1.8 V so the flash stays deselected while the processor pins float after reset (nRF54L15 errata 103) and during power-up and power-down (datasheet section 12).
TP8 to TP10 are test points on the SPI clock, MOSI and MISO lines for the production fixture. WP# (pin 3) and RESET# (pin 7) are left open: both have an internal pull-up while not connected (datasheet section 3, note 1). Use the Reset command if a hardware reset is ever needed.
The two metal pads under the package must stay floating or go to ground only, with no vias or traces under them (datasheet section 19-4). Deep power-down is 0.35 uA maximum.
Open item: land pattern 0.35 x 0.9 mm per pad is drawn from the package outline. Compare with the Macronix recommended land pattern before layout.
